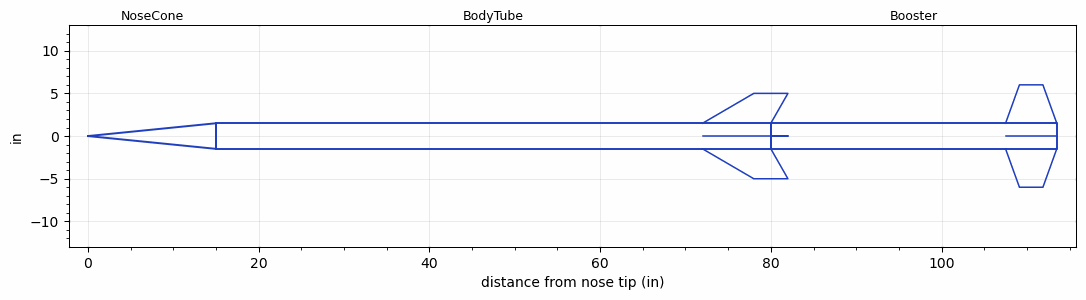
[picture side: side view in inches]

<RASAeroDocument>
 <FileVersion>2</FileVersion>
 <RocketDesign>
  <NoseCone>
   <Length>15</Length>
   <Diameter>3</Diameter>
   <Shape>Conical</Shape>
   <Location>0</Location>
  </NoseCone>
  <BodyTube>
   <Length>65</Length>
   <Diameter>3</Diameter>
   <Location>15</Location>
   <Fin>
    <Count>4</Count>
    <Chord>8</Chord>
    <Span>3.5</Span>
    <SweepDistance>6</SweepDistance>
    <TipChord>4</TipChord>
    <Thickness>0.187</Thickness>
    <LERadius>0.01</LERadius>
    <Location>8</Location>
    <AirfoilSection>Hexagonal</AirfoilSection>
    <FX1>0.75</FX1>
    <FX3>0.75</FX3>
   </Fin>
  </BodyTube>
  <Booster>
   <Length>33.5</Length>
   <Diameter>3</Diameter>
   <InsideDiameter>3</InsideDiameter>
   <Location>80</Location>
   <ShoulderLength>0</ShoulderLength>
   <Fin>
    <Count>4</Count>
    <Chord>6</Chord>
    <Span>4.5</Span>
    <SweepDistance>1.625</SweepDistance>
    <TipChord>2.75</TipChord>
    <Thickness>0.11</Thickness>
    <LERadius>0.01</LERadius>
    <Location>6</Location>
    <AirfoilSection>Hexagonal</AirfoilSection>
    <FX1>0.75</FX1>
    <FX3>0.75</FX3>
   </Fin>
  </Booster>
  <Surface>Rough Camouflage Paint</Surface>
  <ModifiedBarrowman>True</ModifiedBarrowman>
  <Turbulence>True</Turbulence>
  <UseBooster1>False</UseBooster1>
  <UseBooster2>False</UseBooster2>
 </RocketDesign>
 <LaunchSite>
  <Altitude>3700</Altitude>
  <Pressure>29.92</Pressure>
  <RodAngle>1</RodAngle>
  <RodLength>20</RodLength>
  <Temperature>80</Temperature>
  <WindSpeed>5</WindSpeed>
 </LaunchSite>
 <Recovery>
  <Altitude1>1000</Altitude1>
  <Altitude2>1000</Altitude2>
  <DeviceType1>None</DeviceType1>
  <DeviceType2>None</DeviceType2>
  <Event1>False</Event1>
  <Event2>False</Event2>
  <Size1>1</Size1>
  <Size2>1</Size2>
  <EventType1>None</EventType1>
  <EventType2>None</EventType2>
  <CD1>1.33</CD1>
  <CD2>1.33</CD2>
 </Recovery>
 <SimulationList>
  <Simulation>
   <SustainerEngine>3in-N4118  (TsKrush)</SustainerEngine>
   <SustainerLaunchWt>26</SustainerLaunchWt>
   <SustainerCG>50.48</SustainerCG>
   <SustainerIgnitionDelay>10</SustainerIgnitionDelay>
   <Booster1Engine>M2051X  (NotAeroTech)</Booster1Engine>
   <Booster1LaunchWt>36</Booster1LaunchWt>
   <Booster1SeparationDelay>0</Booster1SeparationDelay>
   <Booster1IgnitionDelay>0</Booster1IgnitionDelay>
   <Booster1CG>40</Booster1CG>
   <IncludeBooster1>True</IncludeBooster1>
   <Booster2Delay>0</Booster2Delay>
   <IncludeBooster2>False</IncludeBooster2>
   <TimetoApogee>96.35158</TimetoApogee>
   <MaxAltitude>134933</MaxAltitude>
   <MaxVelocity>4758.434</MaxVelocity>
  </Simulation>
 </SimulationList>
</RASAeroDocument>
